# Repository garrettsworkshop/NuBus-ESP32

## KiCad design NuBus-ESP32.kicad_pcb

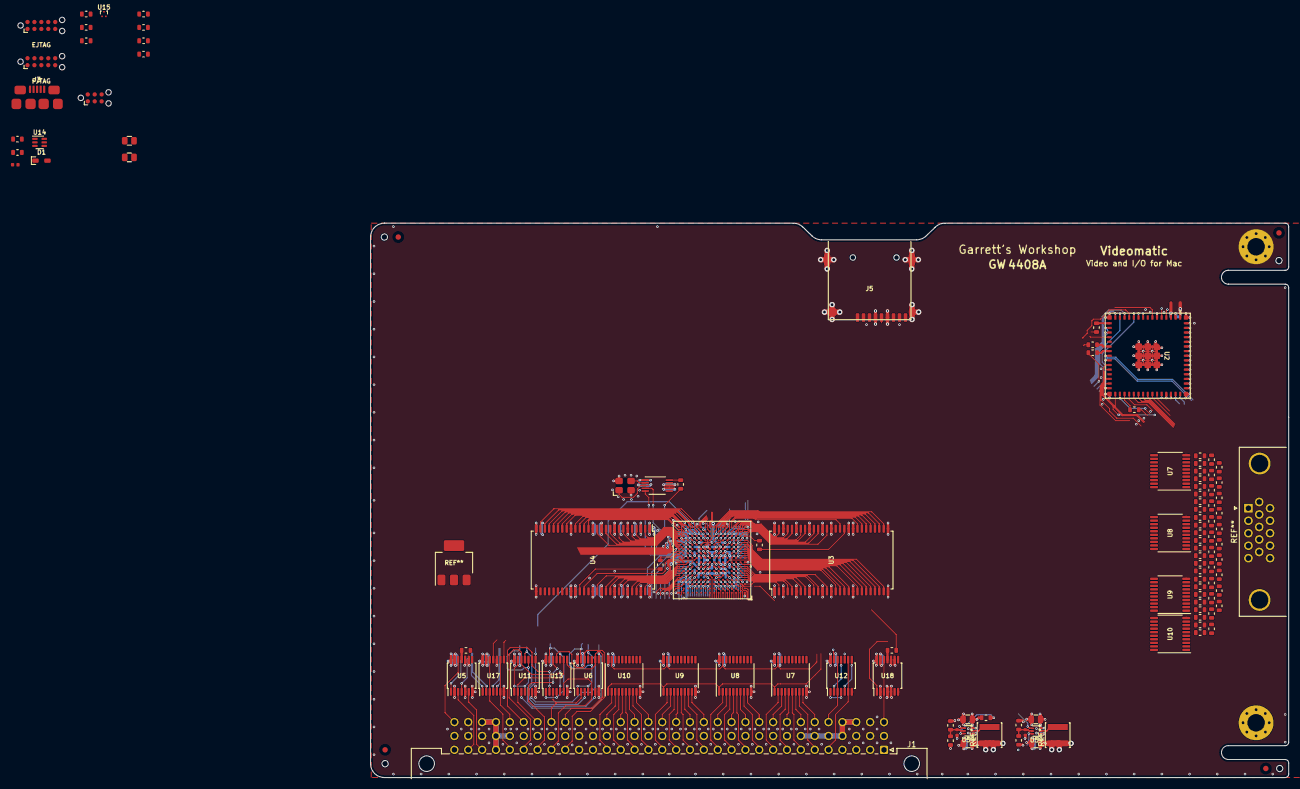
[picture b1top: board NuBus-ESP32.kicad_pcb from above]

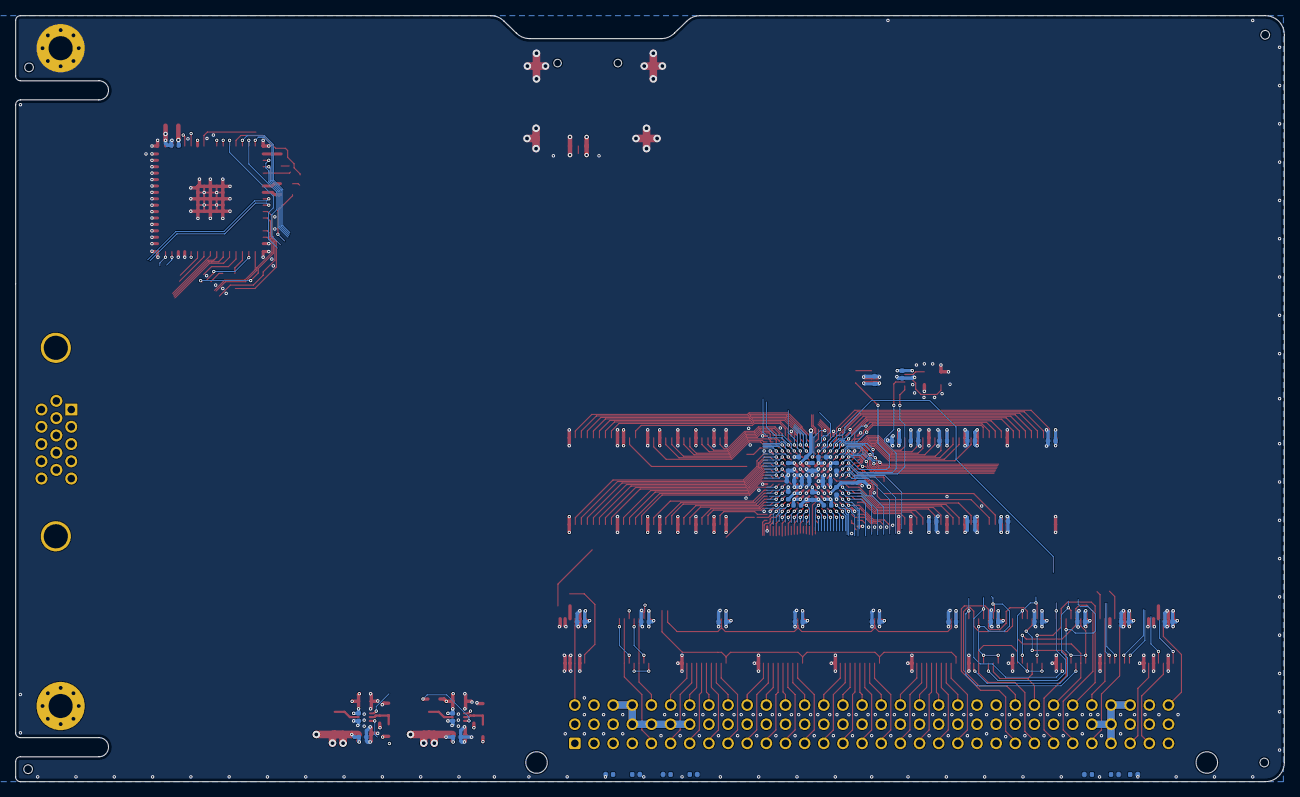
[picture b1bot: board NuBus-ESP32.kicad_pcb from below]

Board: 6 copper layers, 168.3 x 101.6 mm, 71 parts (4 on the bottom side), 215 nets.

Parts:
C1, C5, C8, C10, C15: 100n; C_0402
C7, C9: 22u; C_0805
C11, C12: 4u7; C_0805
C16, C17: 120p; C_0402
C34, C35: 10u; C_0805
D1: Schottky; D_SOD-323
FID1, FID2, FID3, FID4: Fiducial
H1, H2, H3, H4: PasteHole_1.152mm_NPTH
J1: MacNuBus; DIN41612_R_3x32_Male_Horizontal_THT
J2: UART; Tag-Connect_TC2030-IDC-NL_2x03_P1.27mm_Vertical_with_bottom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
J3: microUSB; USB_Micro-B_Amphenol_10118192-0001
J4: EJTAG; Tag-Connect_TC2050-IDC-NL_2x05_P1.27mm_Vertical_with_bottom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
J5: microSD; Xunpu_TF-115_microSD
J6: FJTAG; Tag-Connect_TC2050-IDC-NL_2x05_P1.27mm_Vertical_with_bottom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
R1, R2, R3, R5, R6, R7, R8, R12: 33; R_0603
R4, R11, R13, R14: 68; R_0603
R9, R10: 3k3; R_0603
R17: 15k; R_0603
R18: 17k; R_0603
R19: 56k; R_0603
R20: 12k; R_0603
U1: LFE5U-12F-BG256; Lattice_CABGA-256_14x14mm
U2: ESP32-S2-MINI-2; ESP32-S2-MINI-1U
U3, U4: W9825G6KH-6; TSOP-II-54_22.2x10.16mm_P0.8mm
U5, U6, U11, U12, U13, U17, U18: 74LVC125APW; TSSOP-14_4.4x5mm_P0.65mm
U7, U7#2, U8, U8#2, U9, U9#2, U10, U10#2: 74LVC245APW; TSSOP-20_4.4x6.5mm_P0.65mm
U14: TPS22919; SOT-363
U15: TPD2EUSB30; TI_DRT-3
U16: Si5351A-B-GT; MSOP-10_3x3mm_P0.5mm
U59, U59#2: TPS62A01; SOT-563
Y2: 25M; Crystal_SMD_3225-4Pin_3.2x2.5mm

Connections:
+1V1: U1.G6 (Vcc), U1.G7 (Vcc), U1.G9 (Vcc), U1.L8 (Vcc), U1.L9 (Vcc), U1.L10 (Vcc)
+2V5: U1.G11 (VccAUX), U1.L7 (VccAUX)
+3V3: C8.1, C9.1, C17.1, D1.1 (K), J2.2, J4.1, J6.6, R19.1, U1.F6 (VccIO0), U1.F7 (VccIO0), U1.F10 (VccIO1), U1.F11 (VccIO1), U1.H6 (VccIO7), U1.H7 (VccIO7), U1.H11 (VccIO2), U1.J6 (VccIO6), U1.J7 (VccIO6), U1.J11 (VccIO2), U1.K11 (VccIO3), U1.L6 (VccIO8), U1.L11 (VccIO3), U1.N10 (CFG0), U1.R10 (CFG2), U2.3 (3V3), U3.1 (VDD), U3.3 (VDDQ), U3.9 (VDDQ), U3.14 (VDD), U3.27 (VDD), U3.37 (CKE), U3.43 (VDDQ), U3.49 (VDDQ), U4.1 (VDD), U4.3 (VDDQ), U4.9 (VDDQ), U4.14 (VDD), U4.27 (VDD), U4.37 (CKE), U4.43 (VDDQ), U4.49 (VDDQ), U5.14 (Vcc), U6.14 (Vcc), U7.20 (Vcc), U7#2.20 (Vcc), U8.20 (Vcc), U8#2.20 (Vcc), U9.20 (Vcc), U9#2.20 (Vcc), U10.20 (Vcc), U10#2.20 (Vcc), U11.14 (Vcc), U12.14 (Vcc), U13.14 (Vcc), U14.1 (Vin), U16.1 (VDD), U16.7 (VDDO), U17.14 (Vcc), U18.14 (Vcc)
+5V: C10.1, C11.1, C12.1, C15.1, C34.1, C35.1, J1.A29 (+5V), J1.B4 (+5V), J1.B5 (+5V), J1.B6 (+5V), J1.B7 (+5V), J1.B28 (+5V), J1.B29 (+5V), J1.C3 (+5V), J1.C4 (+5V), J1.C29 (+5V), J1.C30 (+5V), U59.3 (Vin), U59.4 (En), U59#2.3 (Vin), U59#2.4 (En)
/Control/ADDIR: U7.1 (AtoB), U7#2.1 (AtoB), U8.1 (AtoB), U8#2.1 (AtoB), U9.1 (AtoB), U9#2.1 (AtoB), U10.1 (AtoB), U10#2.1 (AtoB)
/Control/AD~OE: U7.19 (~OE), U7#2.19 (~OE), U8.19 (~OE), U8#2.19 (~OE), U9.19 (~OE), U9#2.19 (~OE), U10.19 (~OE), U10#2.19 (~OE)
/Control/ARB~OE: U13.1 (1~OE), U13.4 (2~OE), U13.10 (3~OE), U13.13 (4~OE)
/Control/BARB~OE: U6.1 (1~OE), U6.4 (2~OE), U6.10 (3~OE), U6.13 (4~OE)
/Control/BID~OE: U11.1 (1~OE), U11.4 (2~OE), U11.10 (3~OE), U11.13 (4~OE)
/Control/BTM~OE: U12.10 (3~OE), U12.13 (4~OE)
/Control/B~ACK: U1.E15 (PR8B), U17.11 (4Y)
/Control/B~AD0: U1.B2 (PL2B), U7.11 (B7), U7#2.11 (B7)
/Control/B~AD1: U1.A2 (PT4A), U7.12 (B6), U7#2.12 (B6)
/Control/B~AD2: U1.B3 (PT4B), U7.13 (B5), U7#2.13 (B5)
/Control/B~AD3: U1.A3 (PT6A), U7.14 (B4), U7#2.14 (B4)
/Control/B~AD4: U1.B4 (PT11B), U7.15 (B3), U7#2.15 (B3)
/Control/B~AD5: U1.A4 (PT6B), U7.16 (B2), U7#2.16 (B2)
/Control/B~AD6: U1.B5 (PT15B), U7.17 (B1), U7#2.17 (B1)
/Control/B~AD7: U1.A5 (PT18A), U7.18 (B0), U7#2.18 (B0)
/Control/B~AD8: U1.B6 (PT22B), U8.11 (B7), U8#2.11 (B7)
/Control/B~AD9: U1.A6 (PT18B), U8.12 (B6), U8#2.12 (B6)
/Control/B~AD10: U1.B7 (~PCK01/PT27B), U8.13 (B5), U8#2.13 (B5)
/Control/B~AD11: U1.A7 (PCK00/PT29A), U8.14 (B4), U8#2.14 (B4)
/Control/B~AD12: U1.B8 (~PCK10/PT35B), U8.15 (B3), U8#2.15 (B3)
/Control/B~AD13: U1.A8 (~PCK00/PT29B), U8.16 (B2), U8#2.16 (B2)
/Control/B~AD14: U1.E9 (PT40B), U8.17 (B1), U8#2.17 (B1)
/Control/B~AD15: U1.A9 (PT42A), U8.18 (B0), U8#2.18 (B0)
/Control/B~AD16: U1.B9 (GR10/PT38A), U9.11 (B7), U9#2.11 (B7)
/Control/B~AD17: U1.A10 (PT42B), U9.12 (B6), U9#2.12 (B6)
/Control/B~AD18: U1.B10 (PT44A), U9.13 (B5), U9#2.13 (B5)
/Control/B~AD19: U1.A11 (PT53A), U9.14 (B4), U9#2.14 (B4)
/Control/B~AD20: U1.B11 (PT49A), U9.15 (B3), U9#2.15 (B3)
/Control/B~AD21: U1.A12 (PT53B), U9.16 (B2), U9#2.16 (B2)
/Control/B~AD22: U1.B12 (PT56A), U9.17 (B1), U9#2.17 (B1)
/Control/B~AD23: U1.A13 (PT65A), U9.18 (B0), U9#2.18 (B0)
/Control/B~AD24: U1.B13 (PT60A), U10.11 (B7), U10#2.11 (B7)
/Control/B~AD25: U1.A14 (PT65B), U10.12 (B6), U10#2.12 (B6)
/Control/B~AD26: U1.B14 (PT67A), U10.13 (B5), U10#2.13 (B5)
/Control/B~AD27: U1.A15 (PT67B), U10.14 (B4), U10#2.14 (B4)
/Control/B~AD28: U1.B15 (S0_IN/PR2B), U10.15 (B3), U10#2.15 (B3)
/Control/B~AD29: U1.B16 (PR2A), U10.16 (B2), U10#2.16 (B2)
/Control/B~AD30: U1.C15 (PR5B), U10.17 (B1), U10#2.17 (B1)
/Control/B~AD31: U1.C16 (PR5A), U10.18 (B0), U10#2.18 (B0)
/Control/B~ID_~ARB0: U6.8 (3Y), U11.3 (1Y)
/Control/B~ID_~ARB1: U6.11 (4Y), U11.6 (2Y)
/Control/B~ID_~ARB2: U6.3 (1Y), U11.8 (3Y)
/Control/B~ID_~ARB3: U6.6 (2Y), U11.11 (4Y)
/Control/B~RES: R4.1, U2.10 (IO6)
/Control/B~START: U1.D16 (PR8A), U17.8 (3Y)
/Control/B~TM0: U1.B1 (PL2A), U12.2 (1A), U12.11 (4Y)
/Control/B~TM1: U1.C2 (PL5B), U12.5 (2A), U12.8 (3Y)
/Control/CCLK: U1.N9 (CCLK), U2.21 (IO17)
/Control/CLK: U1.P6 (RPLL0/PL47C), U2.22 (IO18)
/Control/DIN: U1.N8 (M~CS/PB15A), U2.15 (IO11)
/Control/DONE: U1.P9 (DONE), U2.12 (IO8)
/Control/DOUT: U1.M8 (~CSO/PB15B), U2.17 (IO13)
/Control/EIRQ: U1.P5 (~RPLL0/PL47D), U2.11 (IO7)
/Control/FTCK: R13.2, R14.2, U1.T10 (TCK)
/Control/OTM~OE: U12.1 (1~OE), U12.4 (2~OE)
/Control/QD2: U1.P7 (MOSI2/PB6B), U2.18 (IO14)
/Control/QD3: U1.P8 (S~CS1/PB13B), U2.13 (IO9)
/Control/QSCK: U1.P11 (RPLL0/PR47C), U2.16 (IO12)
/Control/Q~CS: U1.N6 (PL47B), U2.14 (IO10)
/Control/RA0: U1.L2 (~PCK61/PL26B), U3.23 (A0)
/Control/RA1: U1.M1 (PCK60/PL26C), U3.24 (A1)
/Control/RA2: U1.M2 (~PCK60/PL26D), U3.25 (A2)
/Control/RA3: U1.N1 (PL32A), U3.26 (A3)
/Control/RA4: U1.T8 (MOSI/PB11B), U3.29 (A4)
/Control/RA5: U1.R8 (S~CS/PB13A), U3.30 (A5)
/Control/RA6: U1.T7 (MISO/PB11A), U3.31 (A6)
/Control/RA7: U1.R7 (MISO2/PB6A), U3.32 (A7)
/Control/RA8: U1.T6 (PB4A), U3.33 (A8)
/Control/RA9: U1.R6 (PB4B), U3.34 (A9)
/Control/RA10: U1.L1 (PCK61/PL26A), U3.22 (A10)
/Control/RA11: U1.R5 (PL44A), U3.35 (A11)
/Control/RBA0: U1.K1 (PCK70/PL23C), U3.20 (BA0)
/Control/RBA1: U1.K2 (~PCK70/PL23D), U3.21 (BA1)
/Control/RCLK: R2.2, U3.38 (CLK)
/Control/RD0: U1.C1 (PL5A), U3.2 (DQ0)
/Control/RD1: U1.D1 (PL8A), U3.4 (DQ1)
/Control/RD2: U1.E2 (PL8B), U3.5 (DQ2)
/Control/RD3: U1.E1 (PL11D), U3.7 (DQ3)
/Control/RD4: U1.F2 (PL11C), U3.8 (DQ4)
/Control/RD5: U1.F1 (PL14A), U3.10 (DQ5)
/Control/RD6: U1.G2 (PL14B), U3.11 (DQ6)
/Control/RD7: U1.G1 (GR71/PL20A), U3.13 (DQ7)
/Control/RD8: U1.P2 (PL32B), U3.42 (DQ8)
/Control/RD9: U1.R1 (Vref16/PL35B), U3.44 (DQ9)
/Control/RD10: U1.R2 (PL38C), U3.45 (DQ10)
/Control/RD11: U1.P3 (PL38B), U3.47 (DQ11)
/Control/RD12: U1.T2 (PL38D), U3.48 (DQ12)
/Control/RD13: U1.R3 (PL41B), U3.50 (DQ13)
/Control/RD14: U1.T3 (PL41D), U3.51 (DQ14)
/Control/RD15: U1.R4 (PL41C), U3.53 (DQ15)
/Control/RDQMH: U1.T4 (PL44B), U3.39 (DQMH)
/Control/RDQML: U1.H2 (PL20B), U3.15 (DQML)
/Control/R~CAS: U1.J1 (PCK71/PL23A), U3.17 (~CAS)
/Control/R~RAS: U1.J2 (~PCK71/PL23B), U3.18 (~RAS)
/Control/R~WE: U1.H5 (PL17A), U3.16 (~WE)
/Control/SCL: U1.L14 (PR32C), U16.4 (SCL)
/Control/SDA: U1.K13 (GR30/PR29A), U16.5 (SDA)
/Control/STRB: U1.E7 (GR00/PT24A), U1.E8 (PCK11/PT33A)
/Control/VA0: U1.R13 (PR41C), U4.23 (A0)
/Control/VA1: U1.T13 (PR44B), U4.24 (A1)
/Control/VA2: U1.M11 (PR47A), U4.25 (A2)
/Control/VA3: U1.R12 (PR44A), U4.26 (A3)
/Control/VA10: U1.N11 (PR47B), U4.22 (A10)
/Control/VBA0: U1.T15 (PR38D), U4.20 (BA0)
/Control/VBA1: U1.T14 (PR41D), U4.21 (BA1)
/Control/VCLK: R6.2, U4.38 (CLK)
/Control/VD0: U1.R16 (Vref13/PR35B), U4.2 (DQ0)
/Control/VD1: U1.P15 (PR32B), U4.4 (DQ1)
/Control/VD2: U1.P16 (PR35A), U4.5 (DQ2)
/Control/VD3: U1.N16 (PR32A), U4.7 (DQ3)
/Control/VD4: U1.M15 (~PCK30/PR26D), U4.8 (DQ4)
/Control/VD5: U1.M16 (PCK30/PR26C), U4.10 (DQ5)
/Control/VD6: U1.L15 (~PCK31/PR26B), U4.11 (DQ6)
/Control/VD7: U1.L16 (PCK31/PR26A), U4.13 (DQ7)
/Control/VD8: U1.J15 (~PCK21/PR23B), U4.42 (DQ8)
/Control/VD9: U1.H15 (PR20B), U4.44 (DQ9)
/Control/VD10: U1.H14 (PR14D), U4.45 (DQ10)
/Control/VD11: U1.G16 (GR21/PR20A), U4.47 (DQ11)
/Control/VD12: U1.G15 (PR14B), U4.48 (DQ12)
/Control/VD13: U1.F16 (PR14A), U4.50 (DQ13)
/Control/VD14: U1.F15 (PR11C), U4.51 (DQ14)
/Control/VD15: U1.E16 (PR11D), U4.53 (DQ15)
/Control/VDQMH: U1.K16 (PCK20/PR23C), U4.39 (DQMH)
/Control/VDQML: U1.P12 (~RPLL0/PR47D), U4.15 (DQML)
/Control/VGACLK: R12.2, U1.L13 (GR31/PR26C)
/Control/VSTRB: U1.J12 (PR17D), U1.J16 (PCK21/PR23A)
/Control/V~CAS: U1.R14 (PR41B), U4.17 (~CAS)
/Control/V~RAS: U1.R15 (PR38C), U4.18 (~RAS)
/Control/V~WE: U1.P14 (PR38B), U4.16 (~WE)
/Control/~PROG: R11.1, U1.R9 (~PROGRAM), U2.19 (IO15)
/D+: J3.3 (D+), U2.24 (IO20), U15.2 (D-)
/D-: J3.2 (D-), U2.23 (IO19), U15.1 (D+)
/ETCK: J4.4, U2.37 (IO41)
/ETDI: J4.8, U2.38 (IO42)
/ETDO: J4.6, U2.35 (IO39)
/ETMS: J4.2, U2.36 (IO40)
/E~DL: J2.6, U2.4 (IO0)
/E~RES: J2.5, J4.10, U2.45 (EN)
/FTCK: J6.1, R14.1
/FTDI: J6.5, U1.R11 (TDI)
/FTDO: J6.7, U1.M10 (TDO)
/FTMS: J6.3, U1.T11 (TMS)
/F~PROG: J6.10, R11.2
/IOP/Mac5Vsense: C1.1, D1.2 (A), R9.2, R10.1, U2.5 (IO1)
/IOP/ORES: U2.7 (IO3), U18.1 (1~OE)
/IOP/SDD1: J5.8 (DAT1), U2.29 (IO34)
/IOP/SDD2: J5.1 (DAT2), U2.28 (IO33)
/IOP/SDMISO_D0: J5.7 (DAT0), U2.31 (IO35)
/IOP/SDMOSI_CMD: J5.3 (CMD), U2.32 (IO36)
/IOP/SDPWR: U2.25 (IO21), U14.3 (En)
/IOP/SDSCK: J5.5 (CLK), U2.33 (IO37)
/IOP/SD~CD: J5.9 (DET), U2.26 (IO26)
/IOP/SD~CS_D3: J5.2 (DAT3/CD), U2.34 (IO38)
/NuBus/CLK: J1.C32 (CLK), U5.12 (4A)
/NuBus/~ACK: J1.A28 (~ACK), U17.3 (1Y), U17.12 (4A)
/NuBus/~AD0: J1.C6 (~AD0), U7.9 (A7), U7#2.9 (A7)
/NuBus/~AD1: J1.A6 (~AD1), U7.8 (A6), U7#2.8 (A6)
/NuBus/~AD2: J1.C7 (~AD2), U7.7 (A5), U7#2.7 (A5)
/NuBus/~AD3: J1.A7 (~AD3), U7.6 (A4), U7#2.6 (A4)
/NuBus/~AD4: J1.C8 (~AD4), U7.5 (A3), U7#2.5 (A3)
/NuBus/~AD5: J1.A8 (~AD5), U7.4 (A2), U7#2.4 (A2)
/NuBus/~AD6: J1.C9 (~AD6), U7.3 (A1), U7#2.3 (A1)
/NuBus/~AD7: J1.A9 (~AD7), U7.2 (A0), U7#2.2 (A0)
/NuBus/~AD8: J1.C10 (~AD8), U8.9 (A7), U8#2.9 (A7)
/NuBus/~AD9: J1.A10 (~AD9), U8.8 (A6), U8#2.8 (A6)
/NuBus/~AD10: J1.C11 (~AD10), U8.7 (A5), U8#2.7 (A5)
/NuBus/~AD11: J1.A11 (~AD11), U8.6 (A4), U8#2.6 (A4)
/NuBus/~AD12: J1.C12 (~AD12), U8.5 (A3), U8#2.5 (A3)
/NuBus/~AD13: J1.A12 (~AD13), U8.4 (A2), U8#2.4 (A2)
/NuBus/~AD14: J1.C13 (~AD14), U8.3 (A1), U8#2.3 (A1)
/NuBus/~AD15: J1.A13 (~AD15), U8.2 (A0), U8#2.2 (A0)
/NuBus/~AD16: J1.C14 (~AD16), U9.9 (A7), U9#2.9 (A7)
/NuBus/~AD17: J1.A14 (~AD17), U9.8 (A6), U9#2.8 (A6)
/NuBus/~AD18: J1.C15 (~AD18), U9.7 (A5), U9#2.7 (A5)
/NuBus/~AD19: J1.A15 (~AD19), U9.6 (A4), U9#2.6 (A4)
/NuBus/~AD20: J1.C16 (~AD20), U9.5 (A3), U9#2.5 (A3)
/NuBus/~AD21: J1.A16 (~AD21), U9.4 (A2), U9#2.4 (A2)
/NuBus/~AD22: J1.C17 (~AD22), U9.3 (A1), U9#2.3 (A1)
/NuBus/~AD23: J1.A17 (~AD23), U9.2 (A0), U9#2.2 (A0)
/NuBus/~AD24: J1.C18 (~AD24), U10.9 (A7), U10#2.9 (A7)
/NuBus/~AD25: J1.A18 (~AD25), U10.8 (A6), U10#2.8 (A6)
/NuBus/~AD26: J1.C19 (~AD26), U10.7 (A5), U10#2.7 (A5)
/NuBus/~AD27: J1.A19 (~AD27), U10.6 (A4), U10#2.6 (A4)
/NuBus/~AD28: J1.C20 (~AD28), U10.5 (A3), U10#2.5 (A3)
/NuBus/~AD29: J1.A20 (~AD29), U10.4 (A2), U10#2.4 (A2)
/NuBus/~AD30: J1.C21 (~AD30), U10.3 (A1), U10#2.3 (A1)
/NuBus/~AD31: J1.A21 (~AD31), U10.2 (A0), U10#2.2 (A0)
/NuBus/~ARB0: J1.C24 (~ARB0), U6.9 (3A), U13.8 (3Y)
/NuBus/~ARB1: J1.A24 (~ARB1), U6.12 (4A), U13.11 (4Y)
/NuBus/~ARB2: J1.C25 (~ARB2), U6.2 (1A), U13.3 (1Y)
/NuBus/~ARB3: J1.A25 (~ARB3), U6.5 (2A), U13.6 (2Y)
/NuBus/~ID0: J1.C26 (~ID0), U11.2 (1A), U13.9 (3A)
/NuBus/~ID1: J1.A26 (~ID1), U11.5 (2A), U13.12 (4A)
/NuBus/~ID2: J1.C27 (~ID2), U11.9 (3A), U13.2 (1A)
/NuBus/~ID3: J1.A27 (~ID3), U11.12 (4A), U13.5 (2A)
/NuBus/~NMRQ: J1.A31 (~NMRQ), U5.3 (1Y)
/NuBus/~RES: J1.C1 (~RESET), U18.3 (1Y), U18.12 (4A)
/NuBus/~RQST: J1.A30 (~RQST), U5.6 (2Y)
/NuBus/~START: J1.C28 (~START), U17.6 (2Y), U17.9 (3A)
/NuBus/~TM0: J1.C5 (~TM0), U12.3 (1Y), U12.12 (4A)
/NuBus/~TM1: J1.A5 (~TM1), U12.6 (2Y), U12.9 (3A)
GND: C1.2, C5.2, C7.2, C8.2, C9.2, C10.2, C11.2, C12.2, C15.2, C34.2, C35.2, J1.A22 (GND), J1.A23 (GND), J1.B2 (GND), J1.B3 (GND), J1.B12 (GND), J1.B13 (GND), J1.B14 (GND), J1.B15 (GND), J1.B16 (GND), J1.B17 (GND), J1.B18 (GND), J1.B19 (GND), J1.B20 (GND), J1.B21 (GND), J1.B22 (GND), J1.B23 (GND), J1.B30 (GND), J1.B31 (GND), J1.C22 (GND), J1.C31 (GND), J2.4, J3.5 (GND), J3.6 (Shield), J4.3, J4.5, J4.7, J5.6 (VSS), J5.10 (SHIELD), J6.2, J6.4, J6.8, R1.2, R10.2, R18.2, R20.2, U1.A1 (GND), U1.A16 (GND), U1.D2 (GND), U1.D15 (GND), U1.F8 (GND), U1.F9 (GND), U1.G8 (GND), U1.G10 (GND), U1.H1 (GND), U1.H8 (GND), U1.H9 (GND), U1.H10 (GND), U1.H16 (GND), U1.J8 (GND), U1.J9 (GND), U1.J10 (GND), U1.K6 (GND), U1.K7 (GND), U1.K8 (GND), U1.K9 (GND), U1.K10 (GND), U1.N2 (GND), U1.N15 (GND), U1.P10 (CFG1), U1.T1 (GND), U1.T5 (GND), U1.T12 (GND), U1.T16 (GND), U2.1 (GND), U2.2 (GND), U2.30 (GND), U2.42 (GND), U2.43 (GND), U2.46 (GND), U2.47 (GND), U2.48 (GND), U2.49 (GND), U2.50 (GND), U2.51 (GND), U2.52 (GND), U2.53 (GND), U2.54 (GND), U2.55 (GND), U2.56 (GND), U2.57 (GND), U2.58 (GND), U2.59 (GND), U2.60 (GND), U2.61 (GND), U2.62 (GND), U2.63 (GND), U2.64 (GND), U2.65 (GND), U3.6 (VSSQ), U3.12 (VSSQ), U3.19 (~CS), U3.28 (VSS), U3.36 (A12), U3.41 (VSS), U3.46 (VSSQ), U3.52 (VSSQ), U3.54 (VSS), U4.6 (VSSQ), U4.12 (VSSQ), U4.19 (~CS), U4.28 (VSS), U4.36 (A12), U4.41 (VSS), U4.46 (VSSQ), U4.52 (VSSQ), U4.54 (VSS), U5.2 (1A), U5.5 (2A), U5.7 (GND), U5.9 (3A), U5.10 (3~OE), U5.13 (4~OE), U6.7 (GND), U7.10 (GND), U7#2.10 (GND), U8.10 (GND), U8#2.10 (GND), U9.10 (GND), U9#2.10 (GND), U10.10 (GND), U10#2.10 (GND), U11.7 (GND), U12.7 (GND), U13.7 (GND), U14.2 (GND), U15.3 (GND), U16.8 (GND), U17.7 (GND), U17.10 (3~OE), U17.13 (4~OE), U18.2 (1A), U18.4 (2~OE), U18.5 (2A), U18.7 (GND), U18.9 (3A), U18.10 (3~OE), U18.13 (4~OE), U59.1 (GND), U59#2.1 (GND), Y2.2, Y2.4
unnamed: J4.9, R1.1
unnamed: R6.1, U1.K15 (~PCK20/PR23D)
unnamed: R2.1, U1.P1 (PL35A)
unnamed: R3.2, U5.11 (4Y)
unnamed: R12.1, U16.10 (CLK0)
unnamed: U16.2 (XA), Y2.3
unnamed: U16.3 (XB), Y2.1
unnamed: R4.2, U18.11 (4Y)
SD3V3: J5.4 (VDD), U14.5 (QOD), U14.6 (Vout)

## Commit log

2021-11-19 Done?
2021-11-19 Create LICENSE
2022-02-06 Export gerbers just to test
2022-03-26 Migrate to KiCAD 6
2022-04-18 did I mess this up?
2022-04-18 Revert "did I mess this up?"
    This reverts commit fd75c937204418059e97b488ea791750328fc4dd.
2022-04-19 Prototype with 74xx
2022-11-04 work on FPGA
2022-11-04 Revert "work on FPGA"
    This reverts commit a96523e8d17974c7c48efc8a38ae046f7948cd49.
